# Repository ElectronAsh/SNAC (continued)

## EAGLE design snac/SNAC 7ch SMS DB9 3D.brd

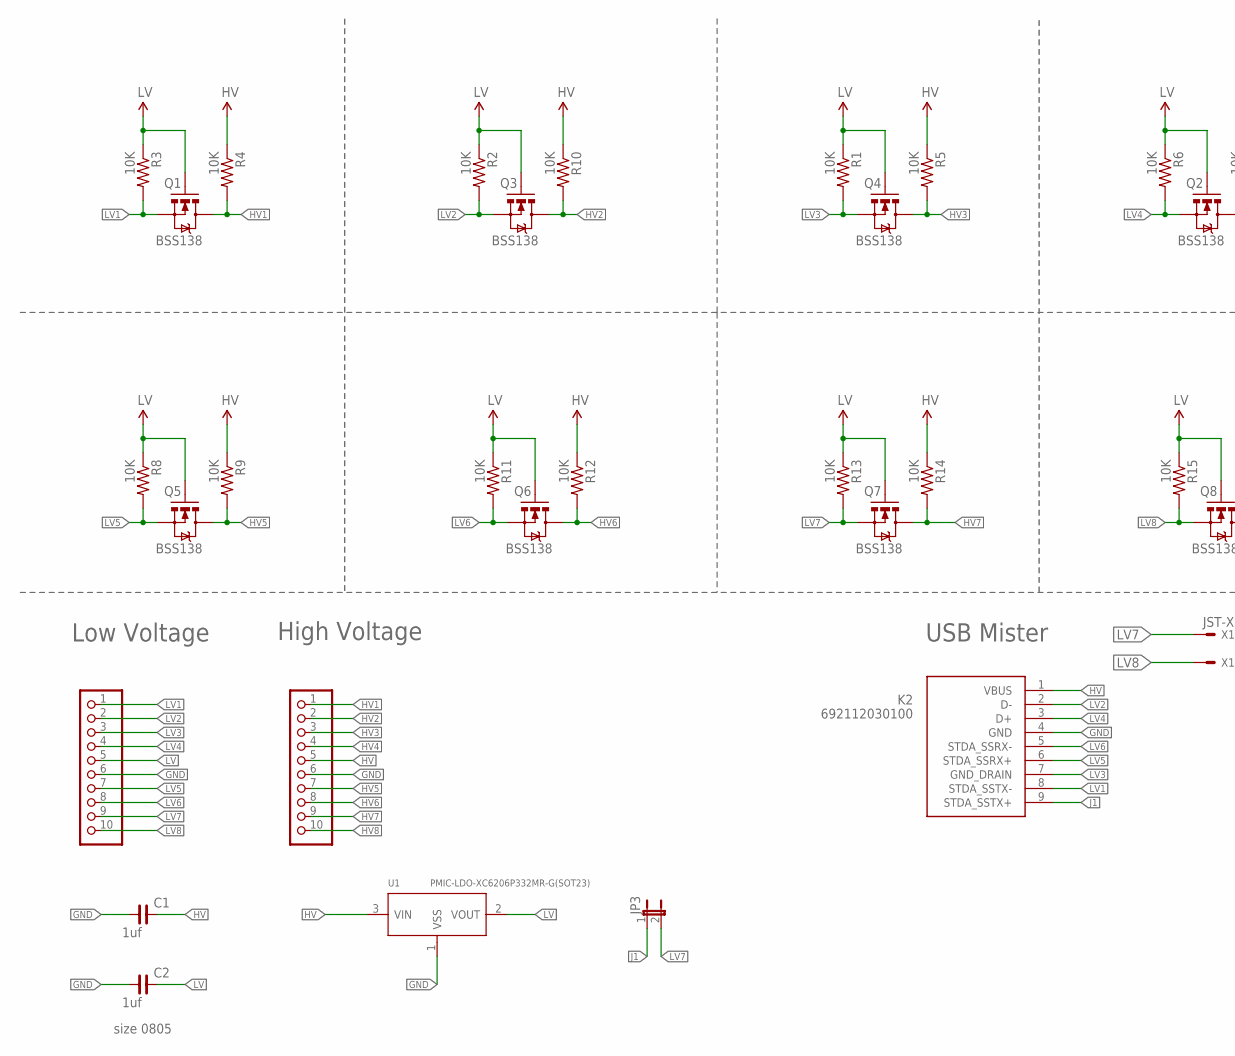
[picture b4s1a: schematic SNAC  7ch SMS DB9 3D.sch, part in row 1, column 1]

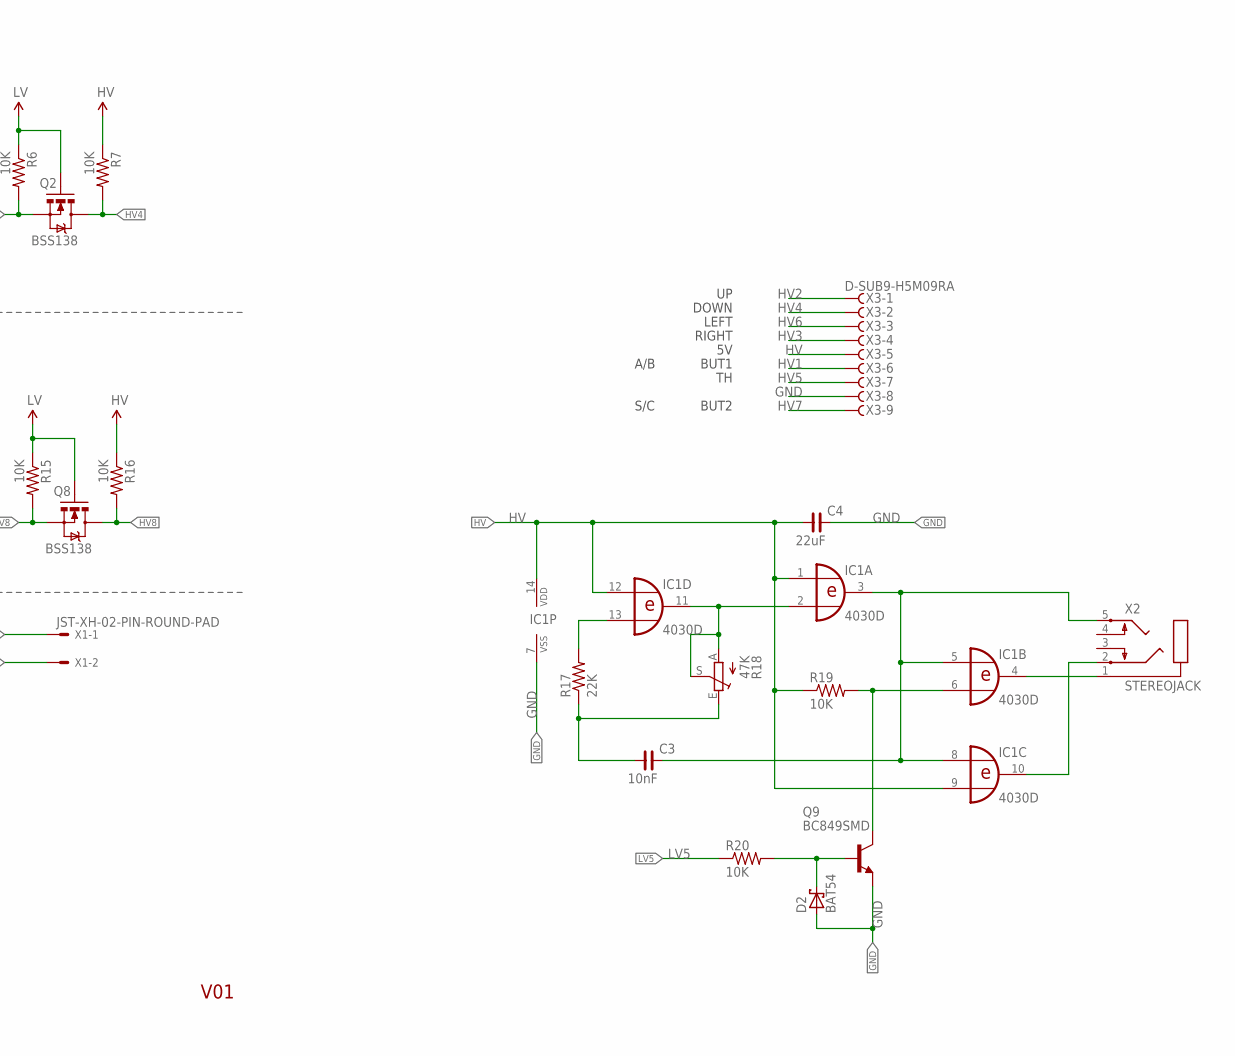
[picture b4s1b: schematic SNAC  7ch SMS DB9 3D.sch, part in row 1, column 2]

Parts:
C1, C2: 1uf; C0805
C3: 10nF; C0805
C4: 22uF; C0805
D2: BAT54; SOT23
IC1: 4030D; SO14
JP1, JP2: PINHD-1X10_2.54-S; 1X10-S
JP3: JUMPER-2PTH; 1X02
K2: 692112030100
Q1, Q2, Q3, Q4, Q5, Q6, Q7, Q8: BSS138; SOT23-3
Q9: BC849SMD; SOT23-BEC
R1, R2, R3, R4, R5, R6, R7, R8, R9, R10, R11, R12, R13, R14, R15, R16, R19, R20: 10K; 0603-RES
R17: 22K; 0603-RES
R18: 47K; B25P
U1: PMIC-LDO-XC6206P332MR-G(SOT23); SOT-23
X1: JST-XH-02-PIN-ROUND-PAD; JST-XH-02-PACKAGE-ROUND-PAD
X2: STEREOJACK; STX3100
X3: D-SUB9-H5M09RA; H5M09RA

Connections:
GND: C1.1, C2.1, C4.2, D2.1 (A), IC1.7 (VSS), JP1.6, JP2.6, K2.4 (GND), Q9.E, U1.1 (VSS), X3.8
HV: C1.2, C4.1, IC1.1 (I0), IC1.9 (I1), IC1.12 (I0), IC1.14 (VDD), JP2.5, K2.1 (VBUS), R4.1, R5.1, R7.1, R9.1, R10.1, R12.1, R14.1, R16.1, R19.1, U1.3 (VIN), X3.5
HV1: JP2.1, Q1.3 (D), R4.2, X3.6
HV2: JP2.2, Q3.3 (D), R10.2, X3.1
HV3: JP2.3, Q4.3 (D), R5.2, X3.4
HV4: JP2.4, Q2.3 (D), R7.2, X3.2
HV5: JP2.7, Q5.3 (D), R9.2, X3.7
HV6: JP2.8, Q6.3 (D), R12.2, X3.3
HV7: JP2.9, Q7.3 (D), R14.2, X3.9
HV8: JP2.10, Q8.3 (D), R16.2
J1: JP3.1, K2.9 (STDA_SSTX+)
LV: C2.2, JP1.5, Q1.1 (G), Q2.1 (G), Q3.1 (G), Q4.1 (G), Q5.1 (G), Q6.1 (G), Q7.1 (G), Q8.1 (G), R1.1, R2.1, R3.1, R6.1, R8.1, R11.1, R13.1, R15.1, U1.2 (VOUT)
LV1: JP1.1, K2.8 (STDA_SSTX-), Q1.2 (S), R3.2
LV2: JP1.2, K2.2 (D-), Q3.2 (S), R2.2
LV3: JP1.3, K2.7 (GND_DRAIN), Q4.2 (S), R1.2
LV4: JP1.4, K2.3 (D+), Q2.2 (S), R6.2
LV5: JP1.7, K2.6 (STDA_SSRX+), Q5.2 (S), R8.2, R20.1
LV6: JP1.8, K2.5 (STDA_SSRX-), Q6.2 (S), R11.2
LV7: JP1.9, JP3.2, Q7.2 (S), R13.2, X1.1
LV8: JP1.10, Q8.2 (S), R15.2, X1.2
unnamed: IC1.2 (I1), IC1.11 (O), R18.A, R18.S
unnamed: C3.2, IC1.3 (O), IC1.5 (I0), IC1.8 (I0), X2.5
unnamed: IC1.4 (O), X2.1
unnamed: IC1.10 (O), X2.2
unnamed: C3.1, R17.1, R18.E
unnamed: IC1.13 (I1), R17.2
unnamed: IC1.6 (I1), Q9.C, R19.2
unnamed: D2.3 (C), Q9.B, R20.2

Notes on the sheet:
High Voltage
Low Voltage
V01
USB Mister
size 0805
DOWN
LEFT
RIGHT
BUT1
BUT2
A/B
S/C

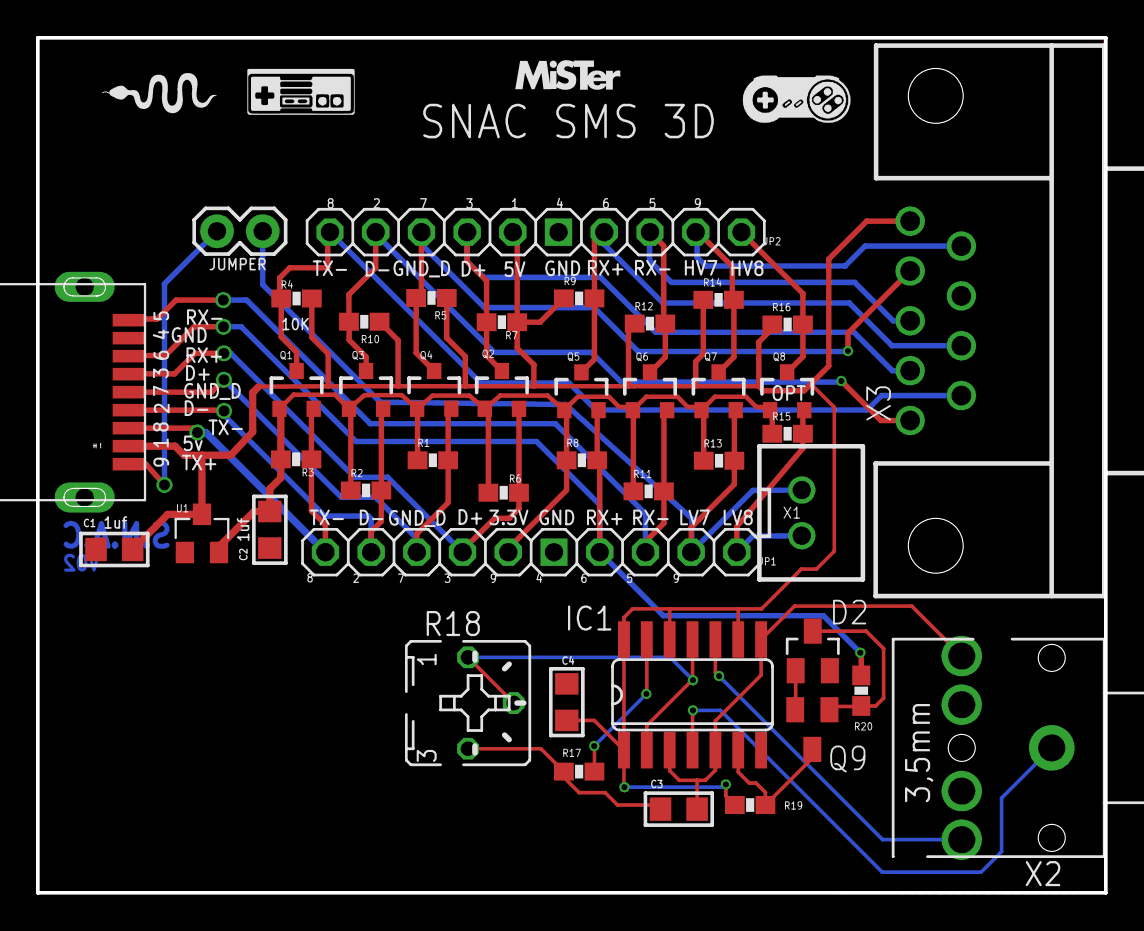
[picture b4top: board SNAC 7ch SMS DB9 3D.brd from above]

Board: 2 copper layers, 59.3 x 47.5 mm, 43 parts (0 on the bottom side), 28 nets.

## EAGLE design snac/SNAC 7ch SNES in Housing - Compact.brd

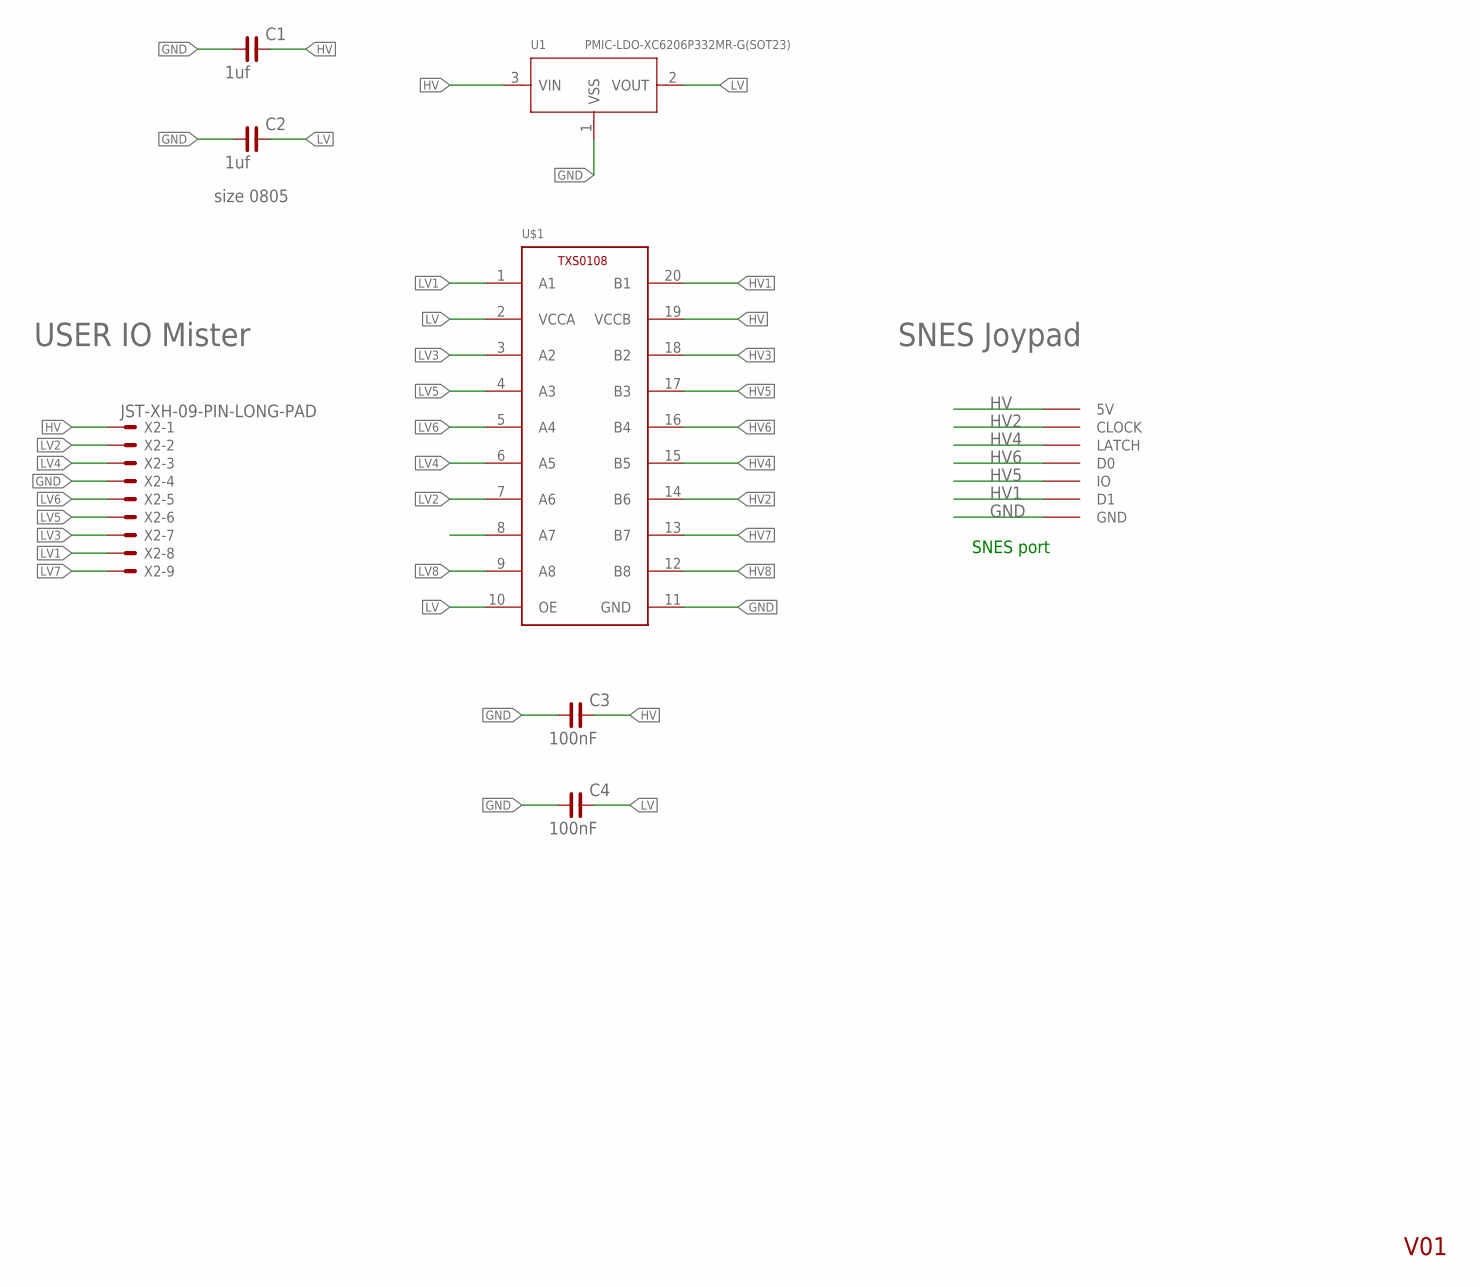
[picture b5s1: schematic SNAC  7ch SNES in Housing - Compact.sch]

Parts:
C1, C2: 1uf; C0805
C3, C4: 100nF; C0805
U1: PMIC-LDO-XC6206P332MR-G(SOT23); SOT-23
U$1: TXS0108; R-PUSON-N20
U$3: SNESCONN
X2: JST-XH-09-PIN-LONG-PAD; JST-XH-09-PACKAGE-LONG-PAD

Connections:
GND: C1.1, C2.1, C3.1, C4.1, U1.1 (VSS), U$1.11 (GND), U$3.GND, X2.4
HV: C1.2, C3.2, U1.3 (VIN), U$1.19 (VCCB), U$3.5V, X2.1
HV1: U$1.20 (B1), U$3.D1
HV2: U$1.14 (B6), U$3.CLOCK
HV3: U$1.18 (B2)
HV4: U$1.15 (B5), U$3.LATCH
HV5: U$1.17 (B3), U$3.IO
HV6: U$1.16 (B4), U$3.D0
HV7: U$1.13 (B7)
HV8: U$1.12 (B8)
LV: C2.2, C4.2, U1.2 (VOUT), U$1.2 (VCCA), U$1.10 (OE)
LV1: U$1.1 (A1), X2.8
LV2: U$1.7 (A6), X2.2
LV3: U$1.3 (A2), X2.7
LV4: U$1.6 (A5), X2.3
LV5: U$1.4 (A3), X2.6
LV6: U$1.5 (A4), X2.5
LV7: X2.9
LV8: U$1.9 (A8)

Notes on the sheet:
V01
USER IO Mister
size 0805
SNES port
SNES Joypad

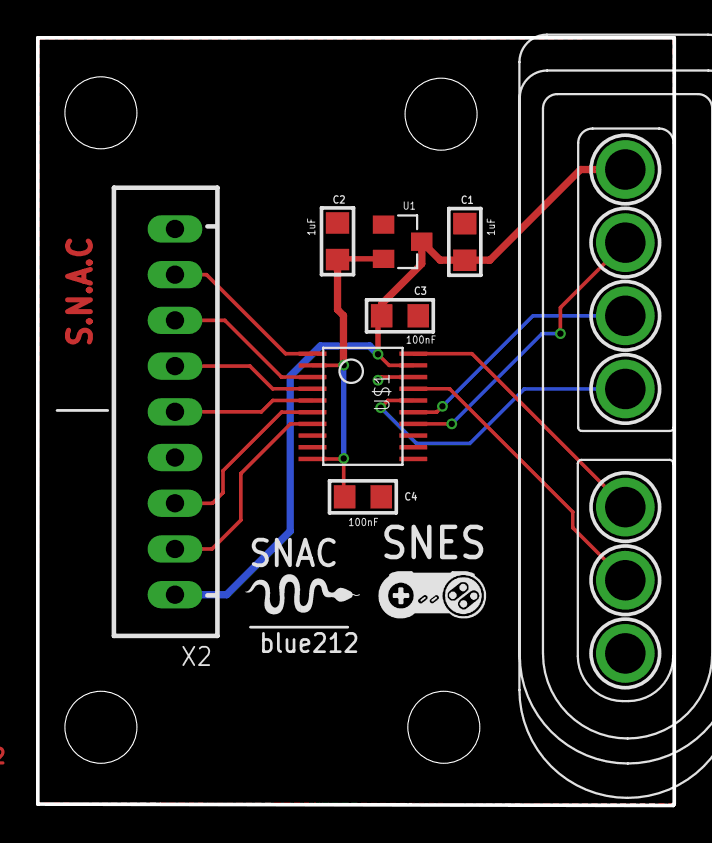
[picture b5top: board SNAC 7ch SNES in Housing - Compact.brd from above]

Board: 2 copper layers, 35.4 x 42.6 mm, 8 parts (0 on the bottom side), 14 nets.

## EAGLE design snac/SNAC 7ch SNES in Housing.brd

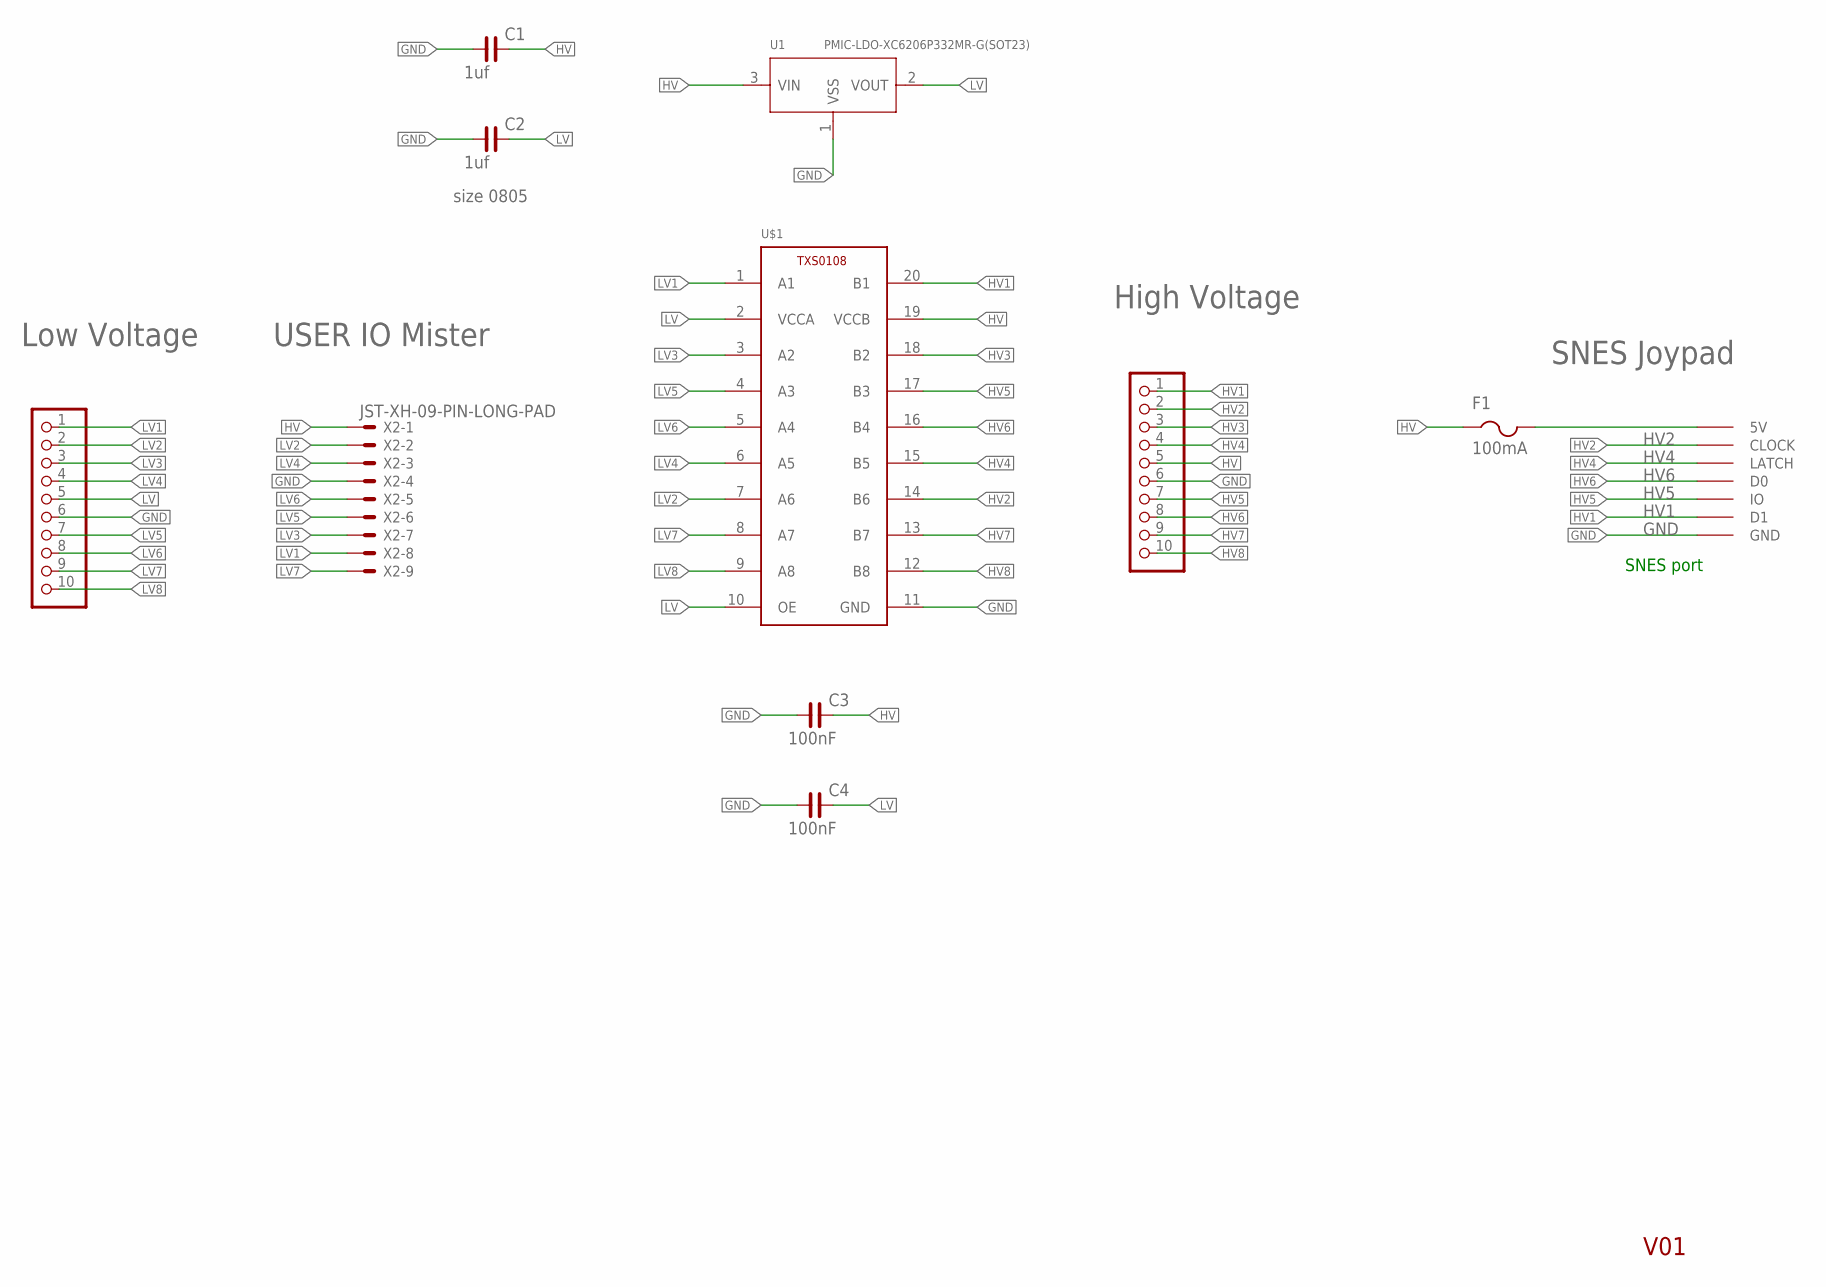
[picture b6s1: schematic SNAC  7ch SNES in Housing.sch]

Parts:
C1, C2: 1uf; C0805
C3, C4: 100nF; C0805
F1: 100mA; R1206
JP1, JP2: PINHD-1X10_2.54-S; 1X10-S
U1: PMIC-LDO-XC6206P332MR-G(SOT23); SOT-23
U$1: TXS0108; R-PUSON-N20
U$3: SNESCONN
X2: JST-XH-09-PIN-LONG-PAD; JST-XH-09-PACKAGE-LONG-PAD

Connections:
GND: C1.1, C2.1, C3.1, C4.1, JP1.6, JP2.6, U1.1 (VSS), U$1.11 (GND), U$3.GND, X2.4
HV1: JP2.1, U$1.20 (B1), U$3.D1
HV2: JP2.2, U$1.14 (B6), U$3.CLOCK
HV3: JP2.3, U$1.18 (B2)
HV4: JP2.4, U$1.15 (B5), U$3.LATCH
HV5: JP2.7, U$1.17 (B3), U$3.IO
HV6: JP2.8, U$1.16 (B4), U$3.D0
HV7: JP2.9, U$1.13 (B7)
HV8: JP2.10, U$1.12 (B8)
LV: C2.2, C4.2, JP1.5, U1.2 (VOUT), U$1.2 (VCCA), U$1.10 (OE)
LV1: JP1.1, U$1.1 (A1), X2.8
LV2: JP1.2, U$1.7 (A6), X2.2
LV3: JP1.3, U$1.3 (A2), X2.7
LV4: JP1.4, U$1.6 (A5), X2.3
LV5: JP1.7, U$1.4 (A3), X2.6
LV6: JP1.8, U$1.5 (A4), X2.5
LV7: JP1.9, X2.9
LV8: JP1.10, U$1.9 (A8)

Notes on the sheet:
High Voltage
Low Voltage
V01
USER IO Mister
size 0805
SNES port
SNES Joypad

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
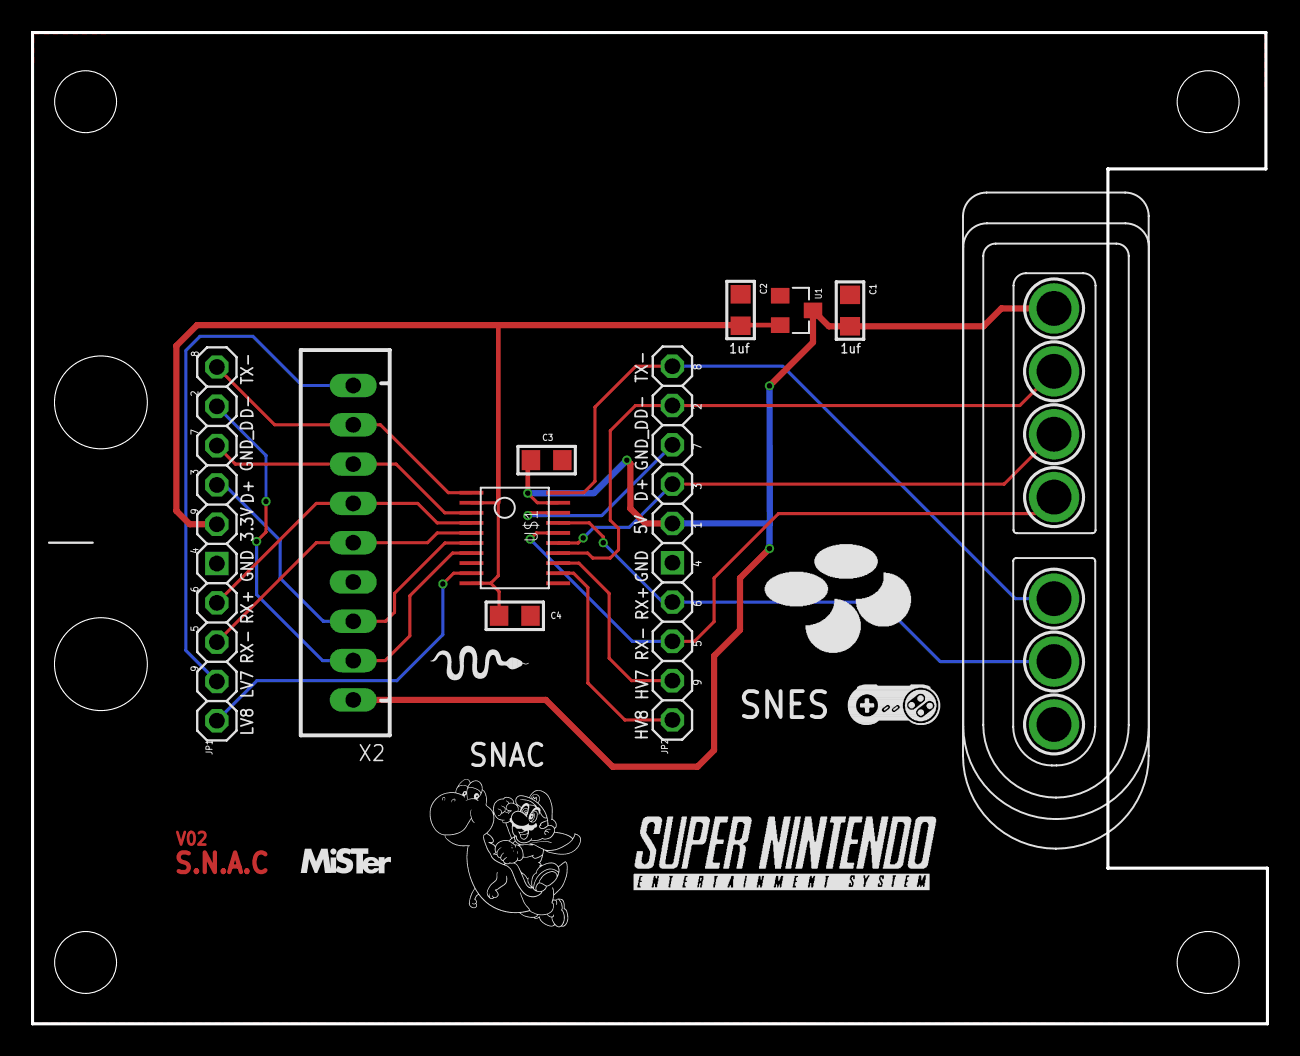
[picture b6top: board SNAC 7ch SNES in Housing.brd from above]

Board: 2 copper layers, 79.8 x 64.1 mm, 10 parts (0 on the bottom side), 19 nets.

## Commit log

2020-11-23 Added version with SMS 3D Glasses driver + DB9
2020-12-07 Added combined voltage translation + SNES joyport
2020-12-07 Add PCB images and other details to the README
2020-12-07 Add PNG files for PCB pics
2020-12-07 README fix
2020-12-07 fix PNG filename
2020-12-07 add missing PNG
2020-12-07 Added ver. with JST XH and SNES joypad, for plastic housing
2020-12-07 Added warning to the README about the untested versions
2020-12-09 Add Compact SNES version, and WIP SNES Multitap
2020-12-09 Added minimal SNES ver, with JST for USER IO. And SMS 3D Dongle
2020-12-09 Changed SMS 3D Dongle back to using LV7 on USER IO
2020-12-13 SMS 3D and SNES SNAC JST updates
2020-12-23 added reversed JST footprint to SNES SNAC Minimal
2020-12-24 Added SMS with 3D glasses driver, JST version
2020-12-24 Updated SMS DB9 with JST version, and PCB image
2021-02-04 changed from LV7 to LV5 pin, for the 3D Glasses boards
2021-02-04 changed from LV7 to LV5 pin on the DB9 3D with JST design
2021-02-12 removed the Compact, TXS chip, and SMS3D with USB3 plug versions
2021-02-12 Updated PCB images and README
2021-02-12 Added missing PCB images
2021-02-12 removed old SNES SNAC version from the README
2021-02-12 update the README
2021-02-13 Added charge pump to the SMS 3D and SMS DB9 3D PCBs
2021-02-13 Updated README to fix missing PNG
2021-02-13 Fixed bottom layer ground pour on SMS 3D Dongle. Updated BOM
2021-03-13 Changed to a MAX660 charge pump on the JST DB9 3D Glasses board
2021-03-13 SMS 3D dongle charge pump and BOM updated
2021-03-13 Removed unneeded diode from the SMS 3D dongle + BOM
2021-03-13 Moved the SNES conn on the JST version to better fit the eBay case
2021-03-18 XOR Osc on 3D boards needed an extra resistor
2021-04-16 New SMS DB9 3D JST rev + BOM done
2021-04-26 removed one cap from the SNES SNAC JST, as it was overkill
2021-05-03 Updated the BOM for the SMS DB9 3D for digikey. Parts were out-of-stock etc.
2021-05-04 fixed major screw-up with the USERIO/JST pinout. Removed the unused FET
2021-06-11 slight tidy of SMS DB9 3D board
2021-06-15 LV6/LV7 selection jumper added to SMS 3D board
2021-06-15 Added note to SMS 3D board about USB 3.0 wire colour swaps
